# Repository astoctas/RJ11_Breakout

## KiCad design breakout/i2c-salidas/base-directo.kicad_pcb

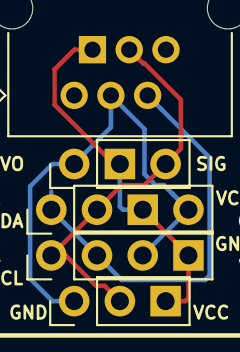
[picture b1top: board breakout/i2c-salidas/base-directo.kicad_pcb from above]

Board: 2 copper layers, 5 parts (0 on the bottom side), 4 nets.

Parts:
J1: RJ9; RJ25_Wayconn_MJEA-660X1_Horizontal
J2, J3: Conn_01x04; PinHeader_1x04_P2.54mm_Vertical
J4: Servo; PinHeader_1x03_P2.54mm_Vertical
J5: Digital; PinHeader_1x03_P2.54mm_Vertical

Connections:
/A0: J1.5, J2.2, J3.1
/D0: J1.4, J2.1, J3.2, J4.3, J5.2
/GND: J1.3, J2.3, J3.4, J4.1, J5.1
/VCC: J1.2, J2.4, J3.3, J4.2, J5.3

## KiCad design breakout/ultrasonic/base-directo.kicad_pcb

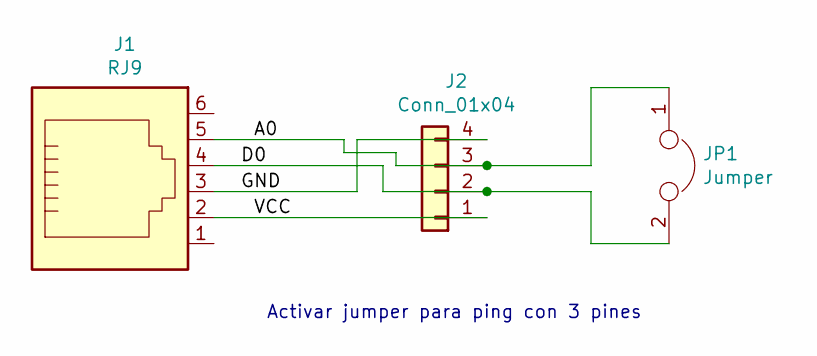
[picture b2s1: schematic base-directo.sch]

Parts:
J1: RJ9; RJ25_Wayconn_MJEA-660X1_Horizontal
J2: Conn_01x04; PinHeader_1x04_P2.54mm_Vertical
JP1: Jumper; PinHeader_1x02_P2.54mm_Vertical

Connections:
/A0: J1.5, J2.3, JP1.1
/D0: J1.4, J2.2, JP1.2
/GND: J1.3, J2.4
/VCC: J1.2, J2.1

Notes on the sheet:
Activar jumper para ping con 3 pines

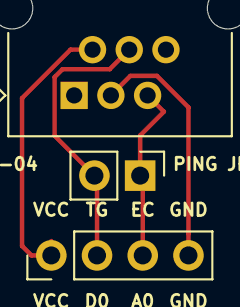
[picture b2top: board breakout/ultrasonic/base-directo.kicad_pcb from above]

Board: 2 copper layers, 3 parts (0 on the bottom side), 4 nets.

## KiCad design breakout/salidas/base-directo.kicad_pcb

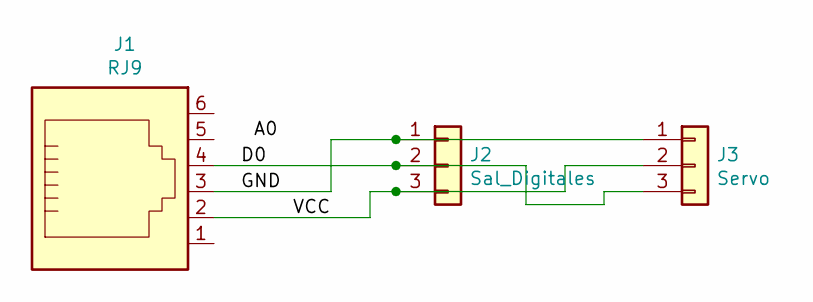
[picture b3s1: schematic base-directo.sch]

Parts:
J1: RJ9; RJ25_Wayconn_MJEA-660X1_Horizontal
J2: Sal_Digitales; PinHeader_1x03_P2.54mm_Vertical
J3: Servo; PinHeader_1x03_P2.54mm_Vertical

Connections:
/D0: J1.4, J2.2, J3.3
/GND: J1.3, J2.1, J3.1
/VCC: J1.2, J2.3, J3.2

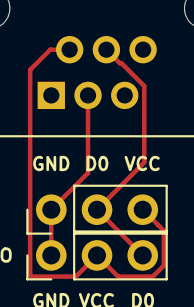
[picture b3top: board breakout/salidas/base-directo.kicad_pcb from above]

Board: 2 copper layers, 3 parts (0 on the bottom side), 3 nets.

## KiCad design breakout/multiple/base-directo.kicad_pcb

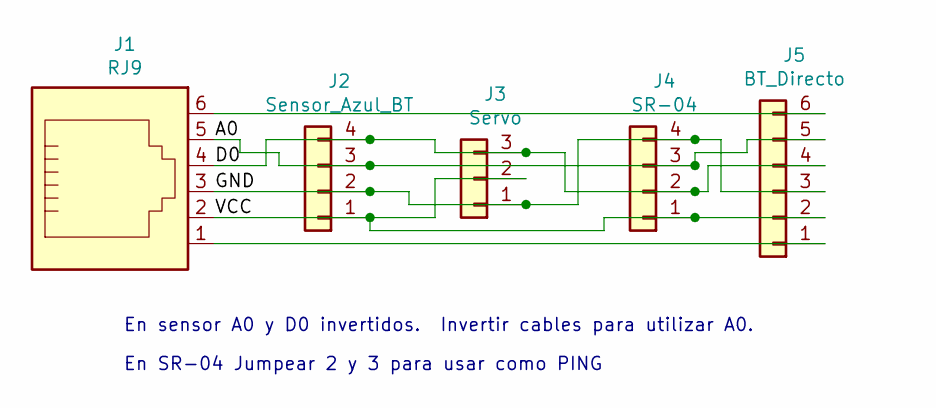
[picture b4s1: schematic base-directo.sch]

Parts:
J1: RJ9; RJ25_Wayconn_MJEA-660X1_Horizontal
J2: Sensor_Azul_BT; PinHeader_1x04_P2.54mm_Vertical
J3: Servo; PinHeader_1x03_P2.54mm_Vertical
J4: SR-04; PinHeader_1x04_P2.54mm_Vertical
J5: BT_Directo; PinHeader_1x06_P2.54mm_Vertical

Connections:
/A0: J1.5, J2.3, J4.3, J5.5
/D0: J1.4, J2.4, J3.3, J4.2, J5.4
/GND: J1.3, J2.2, J3.1, J4.4, J5.3
/VCC: J1.2, J2.1, J3.2, J4.1, J5.2
unnamed: J1.1, J5.1
unnamed: J1.6, J5.6

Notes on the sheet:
En sensor A0 y D0 invertidos. Invertir cables para utilizar A0.
En SR-04 Jumpear 2 y 3 para usar como PING

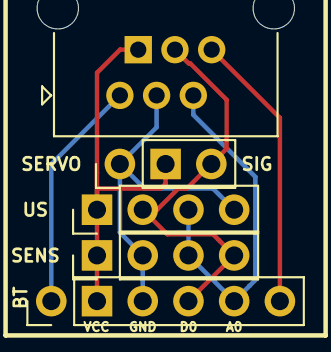
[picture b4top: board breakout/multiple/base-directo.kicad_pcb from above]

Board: 2 copper layers, 5 parts (0 on the bottom side), 6 nets.

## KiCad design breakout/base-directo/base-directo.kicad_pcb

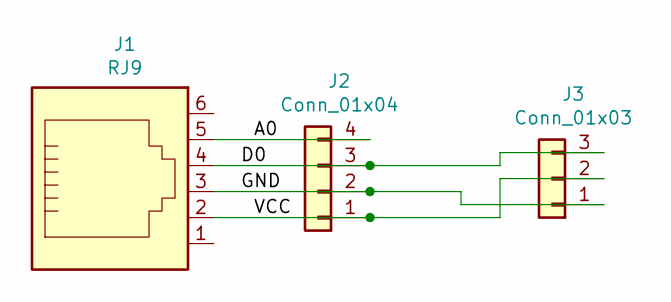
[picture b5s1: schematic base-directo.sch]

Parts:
J1: RJ9; RJ25_Wayconn_MJEA-660X1_Horizontal
J2: Conn_01x04; PinHeader_1x04_P2.54mm_Vertical
J3: Conn_01x03; PinHeader_1x03_P2.54mm_Vertical

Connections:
/A0: J1.5, J2.4
/D0: J1.4, J2.3, J3.3
/GND: J1.3, J2.2, J3.1
/VCC: J1.2, J2.1, J3.2

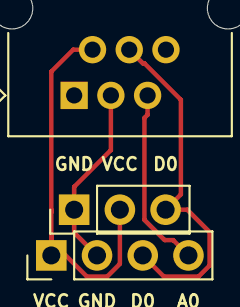
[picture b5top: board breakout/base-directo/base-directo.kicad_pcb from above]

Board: 2 copper layers, 3 parts (0 on the bottom side), 4 nets.

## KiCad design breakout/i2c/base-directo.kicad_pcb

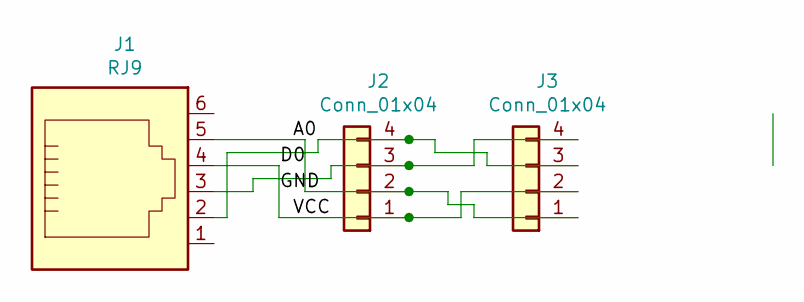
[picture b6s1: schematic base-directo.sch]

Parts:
J1: RJ9; RJ25_Wayconn_MJEA-660X1_Horizontal
J2, J3: Conn_01x04; PinHeader_1x04_P2.54mm_Vertical

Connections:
/A0: J1.5, J2.2, J3.1
/D0: J1.4, J2.1, J3.2
unnamed: J1.2, J2.4, J3.3
unnamed: J1.3, J2.3, J3.4

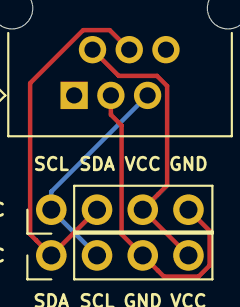
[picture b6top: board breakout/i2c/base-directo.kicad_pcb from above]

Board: 2 copper layers, 3 parts (0 on the bottom side), 4 nets.

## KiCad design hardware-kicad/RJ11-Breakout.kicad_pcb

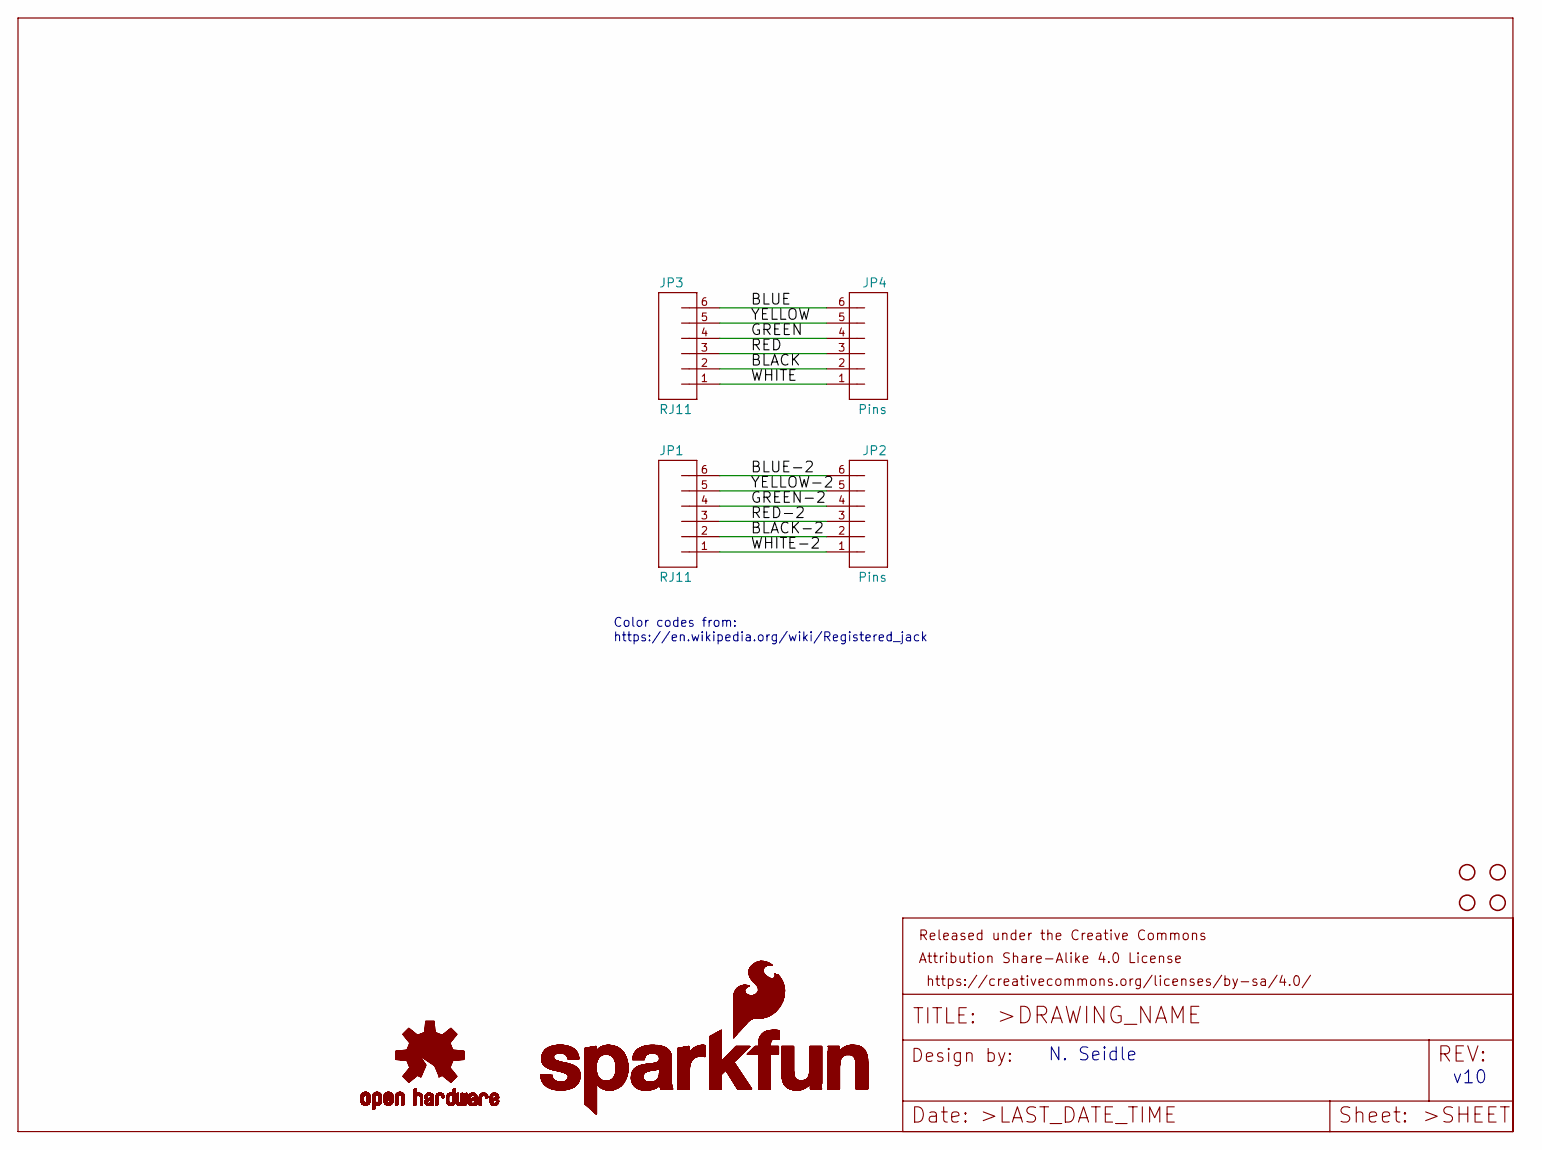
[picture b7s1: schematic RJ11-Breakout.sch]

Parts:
FRAME2: FRAME-LETTER; CREATIVE_COMMONS
H1, H2, H3, H4: STAND-OFF
JP1, JP3: RJ11; RJ11-6
JP2, JP4: Pins; 1X06
LOGO1, LOGO2, LOGO4, LOGO5: SFE_LOGO_NAME_FLAME.1_INCH; SFE_LOGO_NAME_FLAME_.1
LOGO3, LOGO6: OSHW-LOGOMINI; OSHW-LOGO-MINI

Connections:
/BLACK: JP3.2, JP4.2
/BLACK-2: JP1.2, JP2.2
/BLUE: JP3.6, JP4.6
/BLUE-2: JP1.6, JP2.6
/GREEN: JP3.4, JP4.4
/GREEN-2: JP1.4, JP2.4
/RED: JP3.3, JP4.3
/RED-2: JP1.3, JP2.3
/WHITE: JP3.1, JP4.1
/WHITE-2: JP1.1, JP2.1
/YELLOW: JP3.5, JP4.5
/YELLOW-2: JP1.5, JP2.5

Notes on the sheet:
N. Seidle
v10
Color codes from: https://en.wikipedia.org/wiki/Registered_jack

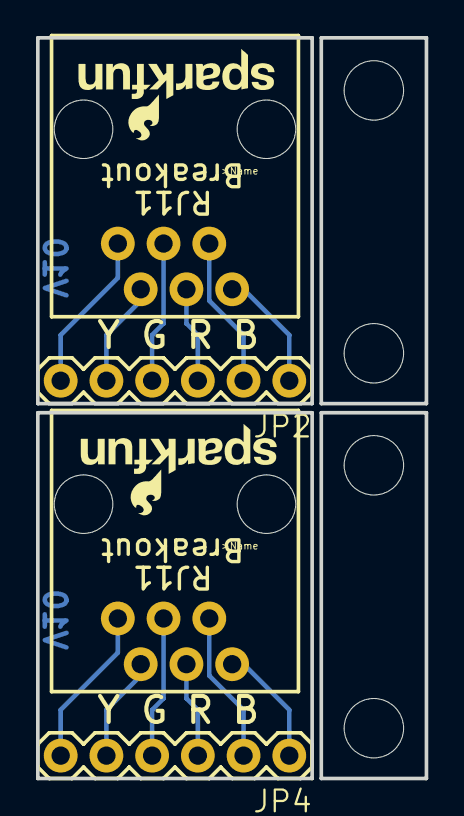
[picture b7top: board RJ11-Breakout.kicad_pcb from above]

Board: 2 copper layers, 21.6 x 41.1 mm, 15 parts (0 on the bottom side), 12 nets.

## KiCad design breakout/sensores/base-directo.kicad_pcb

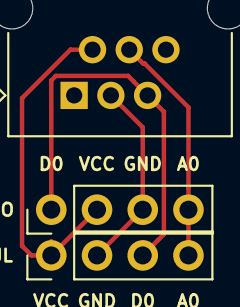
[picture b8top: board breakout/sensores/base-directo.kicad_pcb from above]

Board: 2 copper layers, 3 parts (0 on the bottom side), 4 nets.

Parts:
J1: RJ9; RJ25_Wayconn_MJEA-660X1_Horizontal
J2, J3: Conn_01x04; PinHeader_1x04_P2.54mm_Vertical

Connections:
/D0: J1.4, J2.4, J3.4
/GND: J1.3, J2.2, J3.3
/VCC: J1.2, J2.1, J3.2
unnamed: J1.5, J2.3, J3.1

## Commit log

2020-09-11 RJ11 breakout boards

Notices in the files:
parts and their libraries:
https://creativecommons.org/licenses/by-sa/4.0
Released under the Creative Commons Attribution Share-Alike 4.0 License
